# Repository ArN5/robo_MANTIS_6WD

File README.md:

# robo_MANTIS_6WD
Mantis 6WD robot controlled with Pi 4 and Arduino mega.

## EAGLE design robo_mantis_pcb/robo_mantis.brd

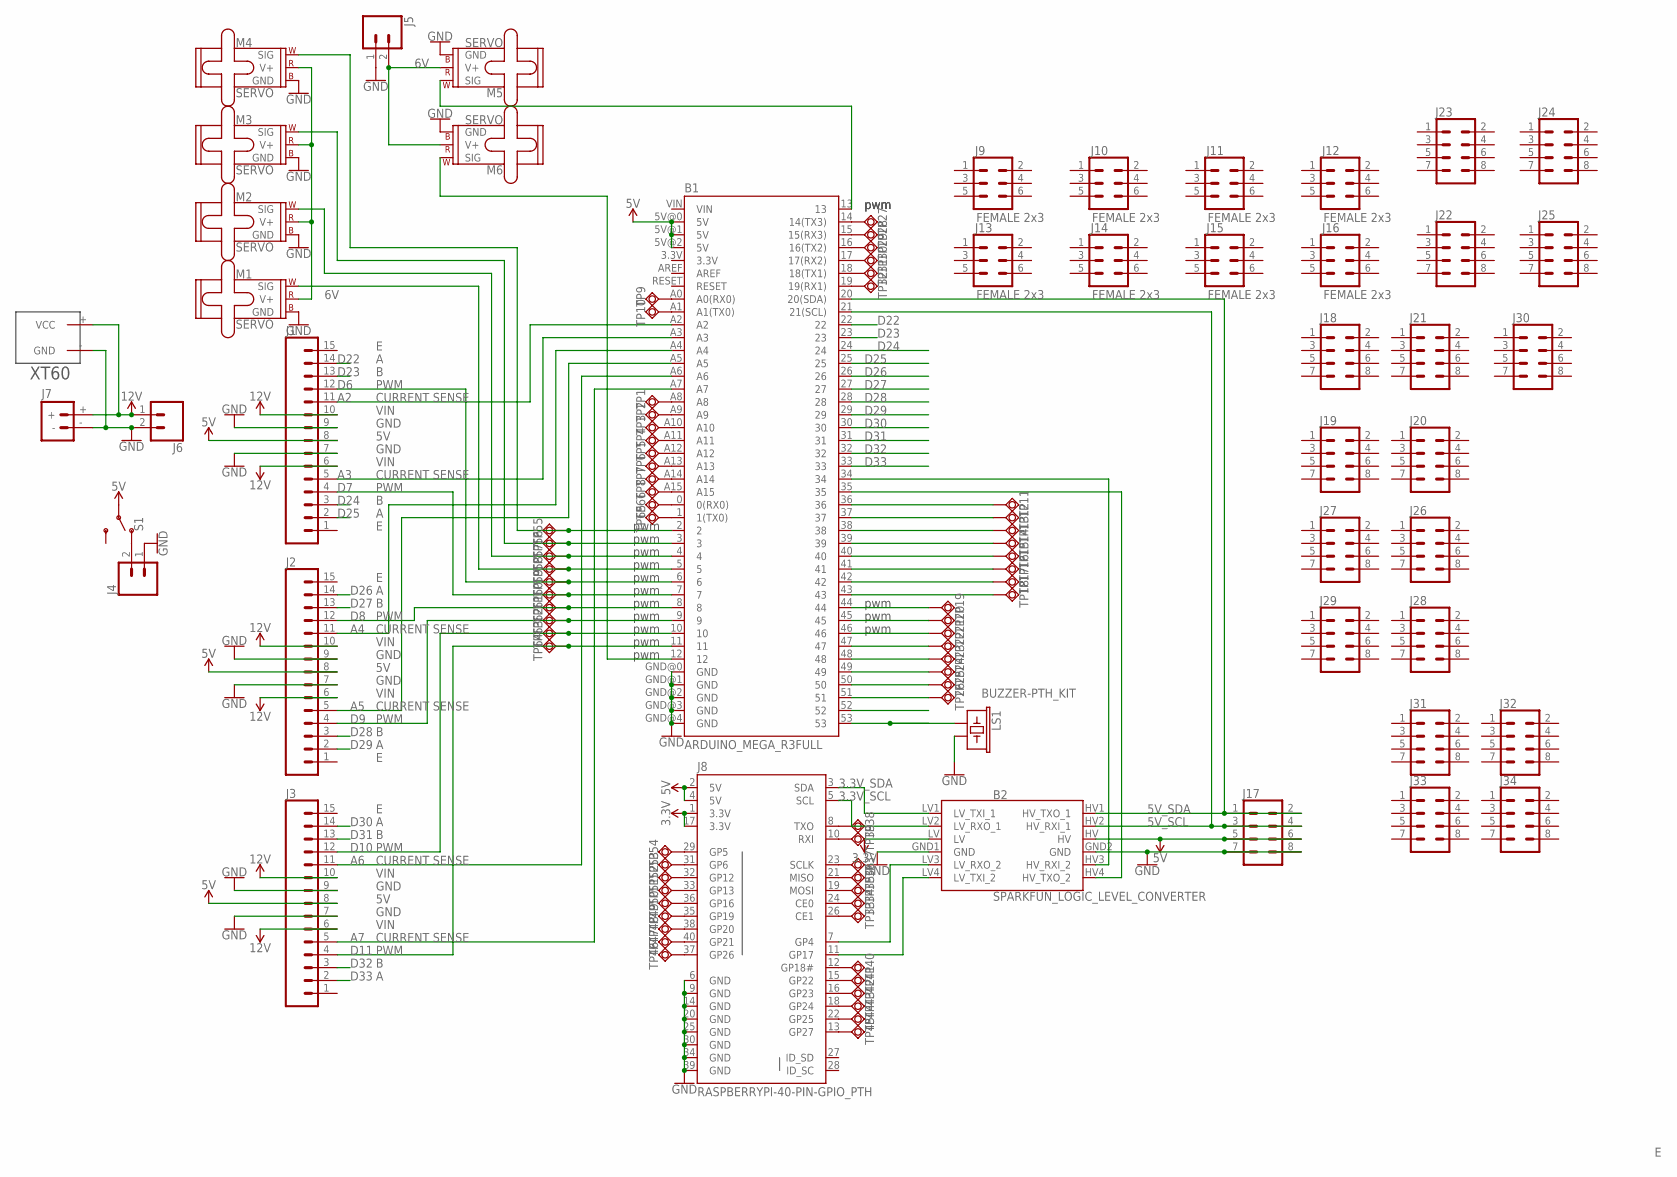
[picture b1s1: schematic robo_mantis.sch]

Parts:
B1: ARDUINO_MEGA_R3FULL; ARDUINO_MEGA
B2: SPARKFUN_LOGIC_LEVEL_CONVERTER
J1, J2, J3: CONN_15LOCK_LONGPADS; 1X15_LOCK_LONGPADS
J4, J5, J6: CONN_02; 1X02
J7: BATTERY_CONN_DEANS; DEANS
J8: RASPBERRYPI-40-PIN-GPIO_PTH; 2X20_SHROUDED
J9, J10, J11, J12, J13, J14, J15, J16: FEMALE 2x3; 2X3
J17, J18, J19, J20, J21, J22, J23, J24, J25, J26, J27, J28, J29, J30, J31, J32, J33, J34: CONN_04X2; 2X4
LS1: BUZZER-PTH_KIT; BUZZER-12MM-KIT
M1, M2, M3, M4, M5, M6: SERVO; 1X03
S1: SWITCH-SPDT-PTH-11.6X4.0MM-LOCK; SWITCH_SPDT_PTH_11.6X4.0MM_LOCK
TP1, TP2, TP3, TP4, TP5, TP6, TP7, TP8, TP9, TP10, TP11, TP12, TP13, TP14, TP15, TP16, TP17, TP18, TP19, TP20, TP21, TP22, TP23, TP24, TP25, TP26, TP27, TP28, TP29, TP30, TP31, TP32, TP33, TP34, TP35, TP36, TP37, TP38, TP39, TP40, TP41, TP42, TP43, TP44, TP45, TP46, TP47, TP48, TP49, TP50, TP51, TP52, TP53, TP54, TP55, TP56, TP57, TP58, TP59, TP60, TP61, TP62, TP63, TP64, TP65, TP66: TESTPAD_TPSQB1,27; TESTPAD_B1,27
U$1: XT60

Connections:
3.3V: B2.LV, J8.1 (3.3V), J8.17 (3.3V)
3.3V_SCL: B2.LV2 (LV_RXO_1), J8.5 (SCL)
3.3V_SDA: B2.LV1 (LV_TXI_1), J8.3 (SDA)
5V: B1.5V@0 (5V), B1.5V@1 (5V), B1.5V@2 (5V), B2.HV, J1.8, J2.8, J3.8, J8.2 (5V), J8.4 (5V), J17.5, J17.6, S1.2
5V_SCL: B1.21 (21(SCL)), B2.HV2 (HV_RXI_1), J17.3, J17.4
5V_SDA: B1.20 (20(SDA)), B2.HV1 (HV_TXO_1), J17.1, J17.2
6V: J5.2, M1.2 (V+), M2.2 (V+), M3.2 (V+), M4.2 (V+), M5.2 (V+), M6.2 (V+)
12V: J1.6, J1.10, J2.6, J2.10, J3.6, J3.10, J6.1, J7.+, U$1.+ (VCC)
A2: B1.A2, J1.11
A3: B1.A3, J1.5
A4: B1.A4, J2.11
A5: B1.A5, J2.5
A6: B1.A6, J3.11
A7: B1.A7, J3.5
BCM4: B2.LV3 (LV_RXO_2), J8.7 (GP4)
BCM17: B2.LV4 (LV_TXI_2), J8.11 (GP17)
D2: B1.2, M4.1 (SIG), TP55.TP
D3: B1.3, M3.1 (SIG), TP56.TP
D4: B1.4, M2.1 (SIG), TP57.TP
D5: B1.5, M1.1 (SIG), TP58.TP
D6: B1.6, J1.12, TP59.TP
D7: B1.7, J1.4, TP60.TP
D8: B1.8, J2.12, TP61.TP
D9: B1.9, J2.4, TP62.TP
D10: B1.10, J3.12, TP63.TP
D11: B1.11, J3.4, TP64.TP
D12: B1.12, M6.1 (SIG)
D13: B1.13, M5.1 (SIG)
D22: B1.22, J1.14
D23: B1.23, J1.13
D24: B1.24, J1.3
D25: B1.25, J1.2
D26: B1.26, J2.14
D27: B1.27, J2.13
D28: B1.28, J2.3
D29: B1.29, J2.2
D30: B1.30, J3.14
D31: B1.31, J3.13
D32: B1.32, J3.3
D33: B1.33, J3.2
GND: B1.GND@0 (GND), B1.GND@1 (GND), B1.GND@2 (GND), B1.GND@3 (GND), B1.GND@4 (GND), B2.GND1 (GND), B2.GND2 (GND), J1.7, J1.9, J2.7, J2.9, J3.7, J3.9, J4.1, J5.1, J6.2, J7.-, J8.6 (GND), J8.9 (GND), J8.14 (GND), J8.20 (GND), J8.25 (GND), J8.30 (GND), J8.34 (GND), J8.39 (GND), J17.7, J17.8, LS1.- (2), M1.3 (GND), M2.3 (GND), M3.3 (GND), M4.3 (GND), M5.3 (GND), M6.3 (GND), U$1.- (GND)
unnamed: B1.44, TP19.TP
unnamed: B1.45, TP20.TP
unnamed: B1.46, TP21.TP
unnamed: B1.47, TP22.TP
unnamed: B1.48, TP23.TP
unnamed: B1.49, TP24.TP
unnamed: B1.50, TP25.TP
unnamed: B1.51, TP26.TP
unnamed: B1.53, LS1.+ (1)
unnamed: J4.2, S1.1 (O)
unnamed: B1.A8, TP1.TP
unnamed: B1.A9, TP2.TP
unnamed: B1.A10, TP3.TP
unnamed: B1.A11, TP4.TP
unnamed: B1.A12, TP5.TP
unnamed: B1.A13, TP6.TP
unnamed: B1.A14, TP7.TP
unnamed: B1.34, B2.HV3 (HV_RXI_2)
unnamed: B1.35, B2.HV4 (HV_TXO_2)
unnamed: B1.36, TP11.TP
unnamed: B1.37, TP12.TP
unnamed: B1.38, TP13.TP
unnamed: B1.39, TP14.TP
unnamed: B1.40, TP15.TP
unnamed: B1.41, TP16.TP
unnamed: B1.42, TP17.TP
unnamed: B1.43, TP18.TP
unnamed: B1.A15, TP8.TP
unnamed: B1.A0 (A0(RX0)), TP9.TP
unnamed: B1.A1 (A1(TX0)), TP10.TP
unnamed: B1.14 (14(TX3)), TP27.TP
unnamed: B1.15 (15(RX3)), TP28.TP
unnamed: B1.16 (16(TX2)), TP29.TP
unnamed: B1.17 (17(RX2)), TP30.TP
unnamed: B1.18 (18(TX1)), TP31.TP
unnamed: B1.19 (19(RX1)), TP32.TP
unnamed: J8.26 (CE1), TP33.TP
unnamed: J8.24 (CE0), TP34.TP
unnamed: J8.19 (MOSI), TP35.TP
unnamed: J8.21 (MISO), TP36.TP
unnamed: J8.23 (SCLK), TP37.TP
unnamed: J8.8 (TXO), TP38.TP
unnamed: J8.10 (RXI), TP39.TP
unnamed: J8.12 (GP18#), TP40.TP
unnamed: J8.15 (GP22), TP41.TP
unnamed: J8.16 (GP23), TP42.TP
unnamed: J8.18 (GP24), TP43.TP
unnamed: J8.22 (GP25), TP44.TP
unnamed: J8.13 (GP27), TP45.TP
unnamed: J8.37 (GP26), TP46.TP
unnamed: J8.40 (GP21), TP47.TP
unnamed: J8.38 (GP20), TP48.TP
unnamed: J8.35 (GP19), TP49.TP
unnamed: J8.36 (GP16), TP50.TP
unnamed: J8.33 (GP13), TP51.TP
unnamed: J8.32 (GP12), TP52.TP
unnamed: J8.31 (GP6), TP53.TP
unnamed: J8.29 (GP5), TP54.TP
unnamed: B1.1 (1(TX0)), TP65.TP
unnamed: B1.0 (0(RX0)), TP66.TP

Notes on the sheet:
VIN
CURRENT SENSE
PWM
GND
pwm

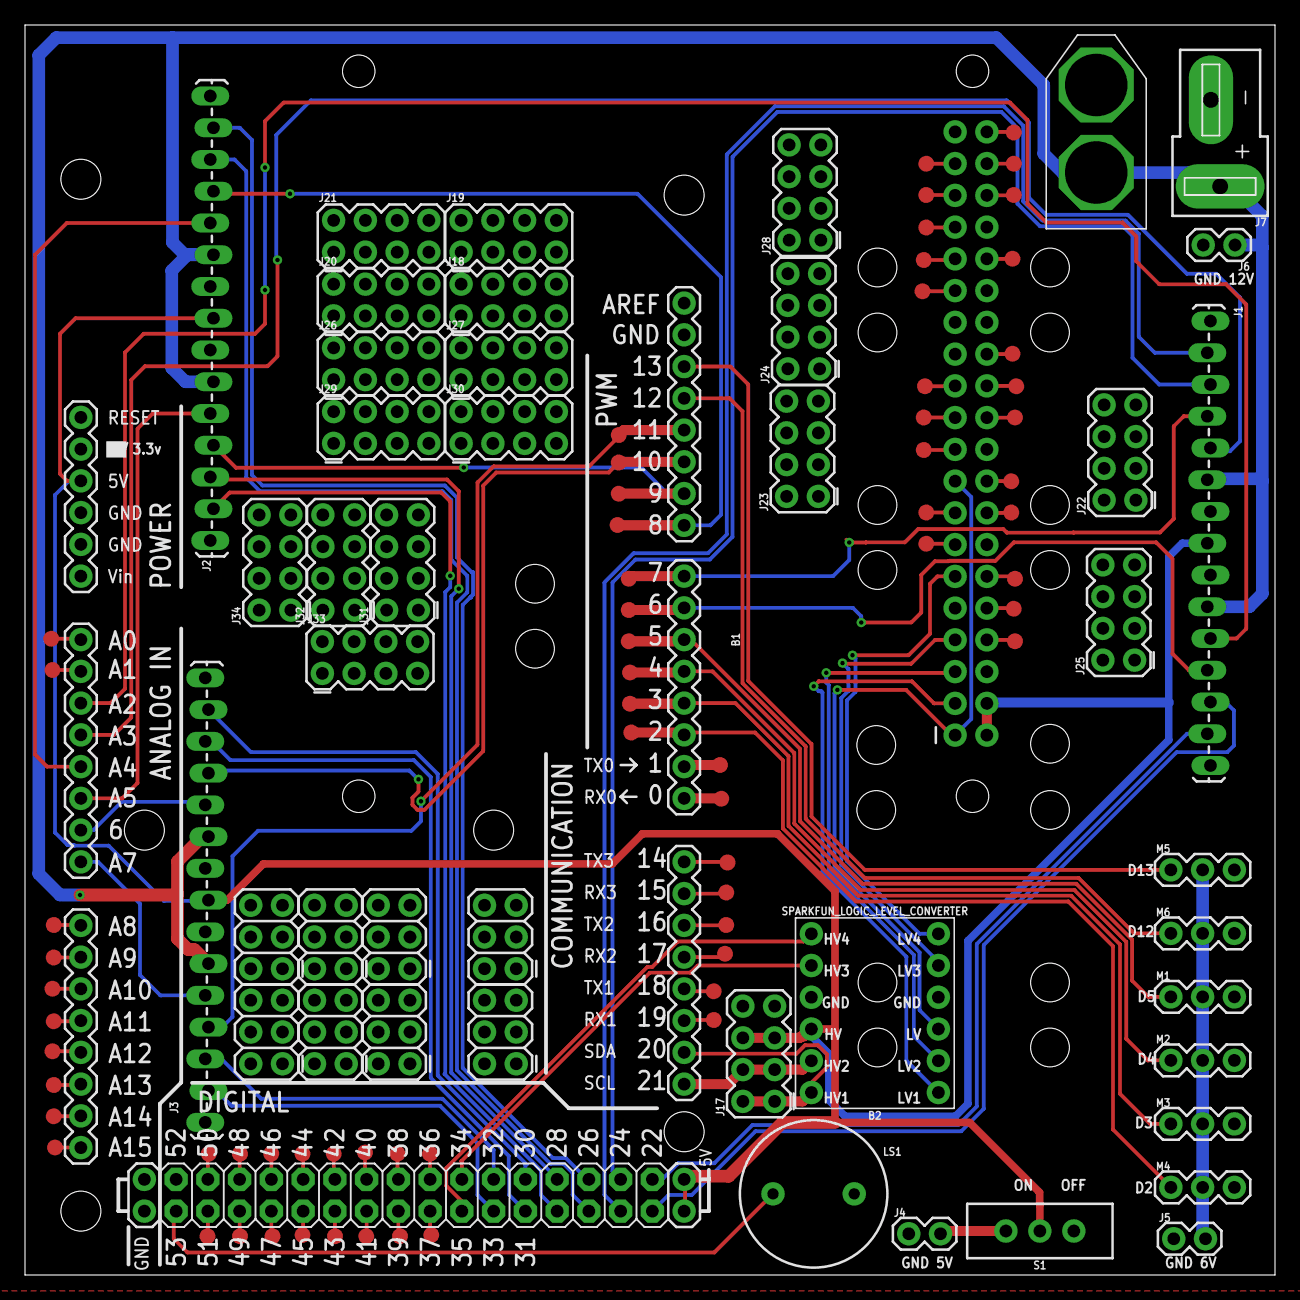
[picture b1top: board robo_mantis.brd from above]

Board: 2 copper layers, 99.9 x 99.9 mm, 111 parts (1 on the bottom side), 101 nets.

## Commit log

2020-03-06 adding pcb files and arduino mega code
2020-08-17 some changes to PCB files
2020-08-17 update arduino file servo and I2C comm.
    added servo positions for my robots configuration. Also added the I2C communication protocol.
2020-09-02 PI I2C code
    drive code on Pi side that can send I2C commands using smbus
2020-09-06 added code for servos & current sense
2020-09-06 added python side code for servo control
2020-09-06 added new motor stop & cleaned up code
2020-09-20 Fixes to I2C and Current sense
    -lowered the I2C baud rate to match PI 3 I2C rate.
    -Fixed the output array for the current sensor reading. they just send over the analogread value divided by 4.
2020-09-20 Added jupyter notebook with Tests
2020-09-20 cleaned up file
    removed extra commands left over from jupyter notebook

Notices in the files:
parts and their libraries:
SparkFun-Connectors: Licensing: Creative Commons ShareAlike 4.0 International - https://creativecommons.org/licenses/by-sa/4.0
